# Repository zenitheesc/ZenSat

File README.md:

<h1 align="center" style="color:white; background-color:black">ZenSat</h1>
<h4 align="center">This is an Open Hardware and Software CubeSat developed by Zenith EESC-USP for the CubeDesign 2018.</h4>

<p align="center">

</p>

Aiming to participate in the first CubeDesign in 2018, Zenith designed its first nanosatellite prototype, which was named ”ZenSat”. This project was a 2U CubeSat for imaging missions in the competition. It is worth mentioning that the focus of the project was not to validate a nanosatellite for flight but to enable a first contact between the group members and the development of a nanosatellite.

<a href="https://github.com/zenitheesc/ZenSat_1.0/tree/master/ADC%20-%20Attitude%20Determination%20and%20Control"><h2> ADC - Attitude Determination and Control </h2></a>
The entire stabilization and pointing system must be done necessary to fulfill the competition missions. For this, the reading is done necessary sensors, activating a reaction wheel, which, by means of the Law of Conservation of Angular Momentum, manages to act in the attitude of the satellite.

<a href="https://github.com/zenitheesc/ZenSat_1.0/tree/master/COM%20-%20Command%20and%20Telemetry"><h2>COM - Command and Telemetry</h2></a>
It is responsible by the bidirectional telemetry in cubesat. This System has two LoRa radios, which communicate with the CTRL Subsystem

<a href="https://github.com/zenitheesc/ZenSat_1.0/tree/master/COM%20-%20Command%20and%20Telemetry"><h2>CTRL - Control</h2></a>
The Control System is the main component of the project. This system is responsible for data analysis, decision making and controlling the others systems

<a href="https://github.com/zenitheesc/ZenSat_1.0/tree/master/PS%20-%20Power%20Supply"><h2>PS - Power Supply</h2></a>
Ensures the monitoring and control of EPS panel parameters,
that is, it performs the measurement of voltage and current levels at various points on the CubeSat;
monitors the temperature of the batteries and acts to keep it always positive, in addition to
carry out communication with other subsystems.
Also it performs conversions of battery voltage levels to the levels requested within the
hardware, making the necessary distribution, as well as controlling the loading of batteries through solar panels.

<a href="https://github.com/zenitheesc/ZenSat_1.0/tree/master/STT%20-%20Structure"><h2> STT - Structure </h2></a>
Finally, we have the subsystem responsible for the physical integration of all
the subsystems described earlier. All manufacturing issues involving
the physical structure of ZenSat is the responsibility of the structures subsystem. The
determination of the materials used, the choice of manufacturing processes and display of all components, aiming at a satisfactory performance in the
vibration, are the main focuses of this subsystem

## Official Documentation

Check out the official documentation [here](https://github.com/zenitheesc/ZenSat_1.0/blob/master/ZenSat%20v.1.0.pdf).

<p align="center">

</p>
<p align = "center">
<a href="zenith.eesc@gmail.com">zenith.eesc@gmail.com</a>
</p>

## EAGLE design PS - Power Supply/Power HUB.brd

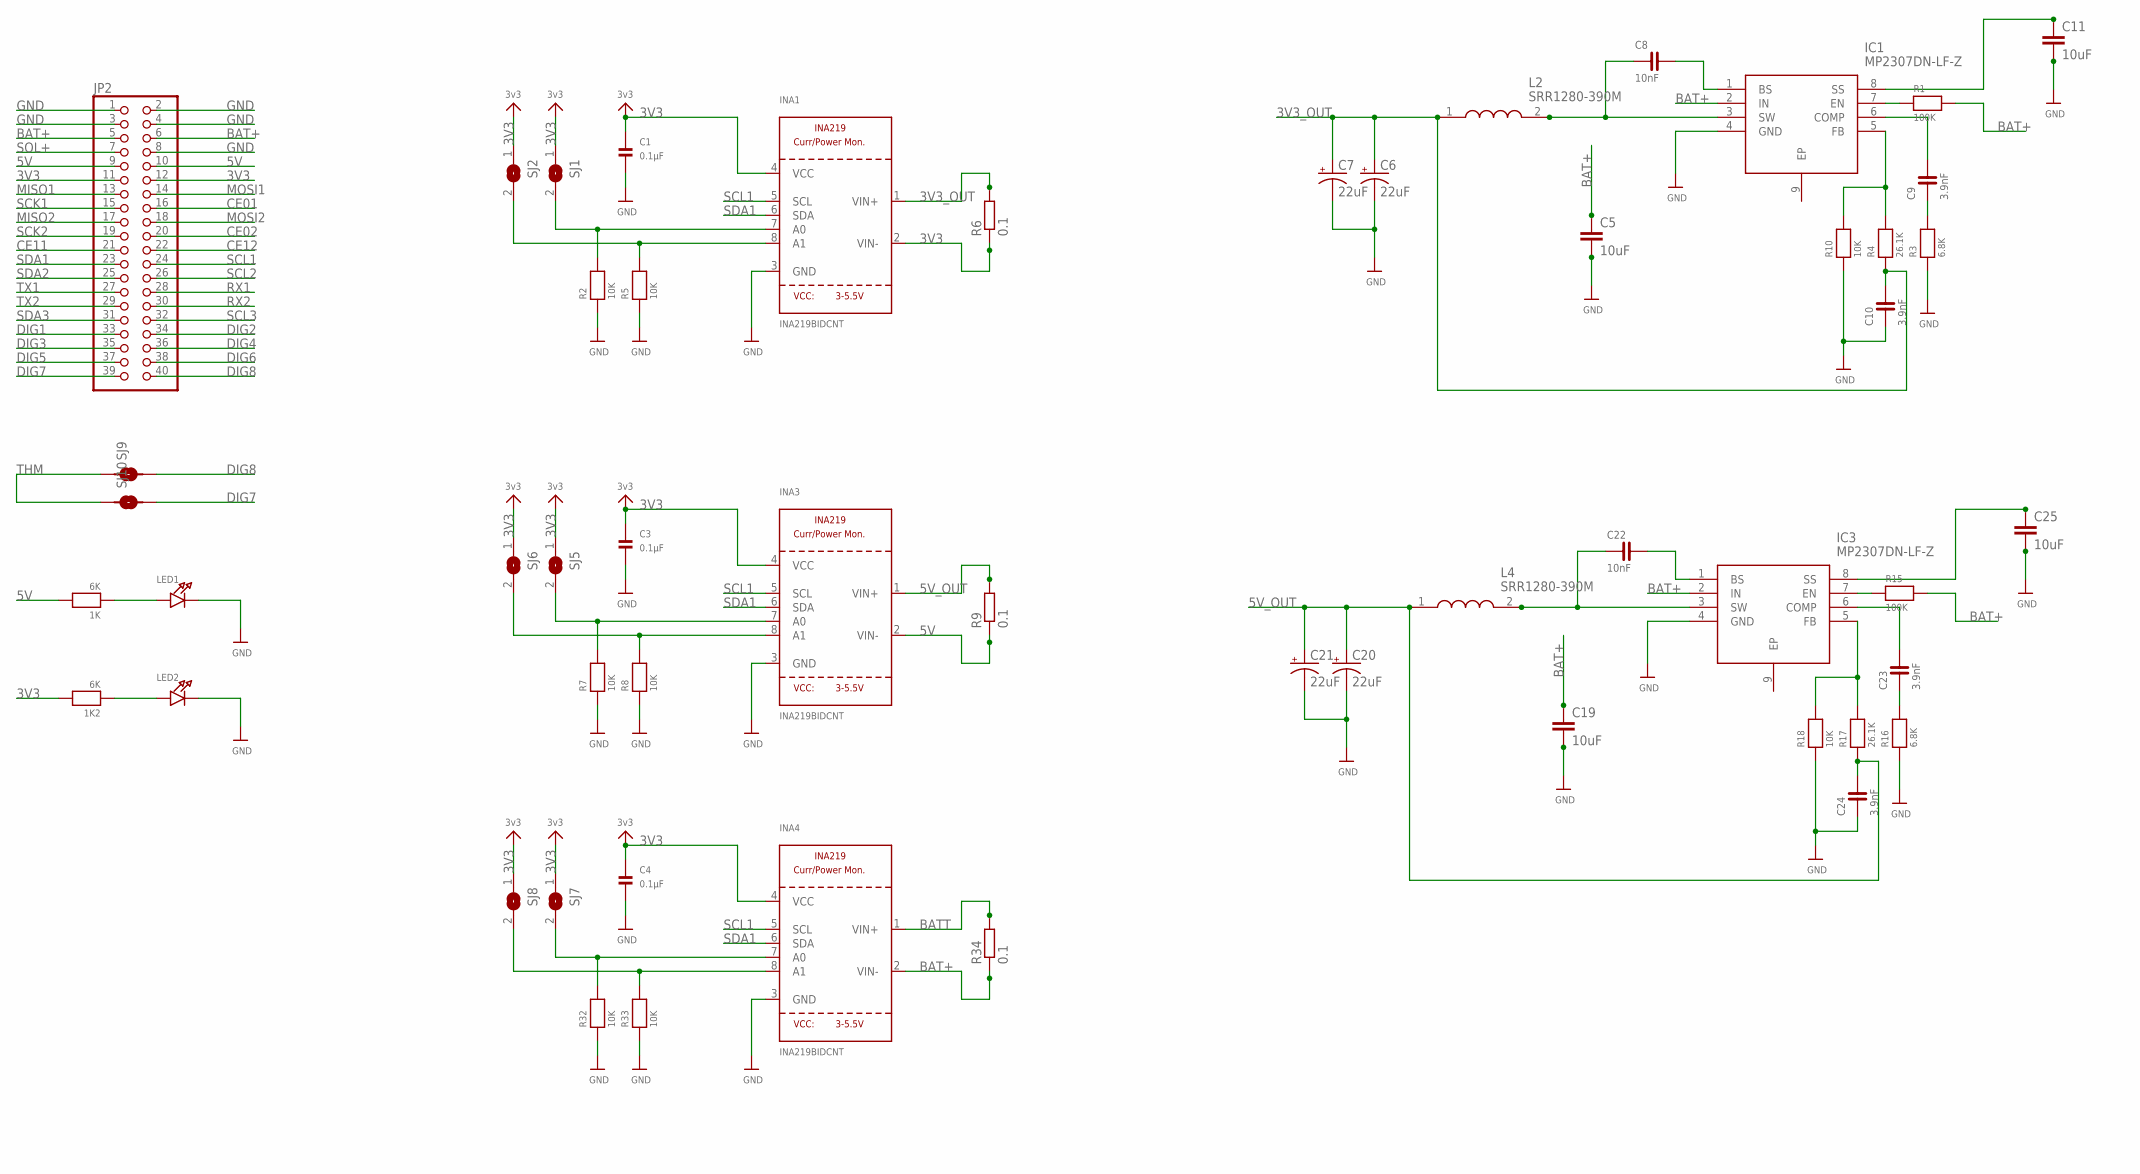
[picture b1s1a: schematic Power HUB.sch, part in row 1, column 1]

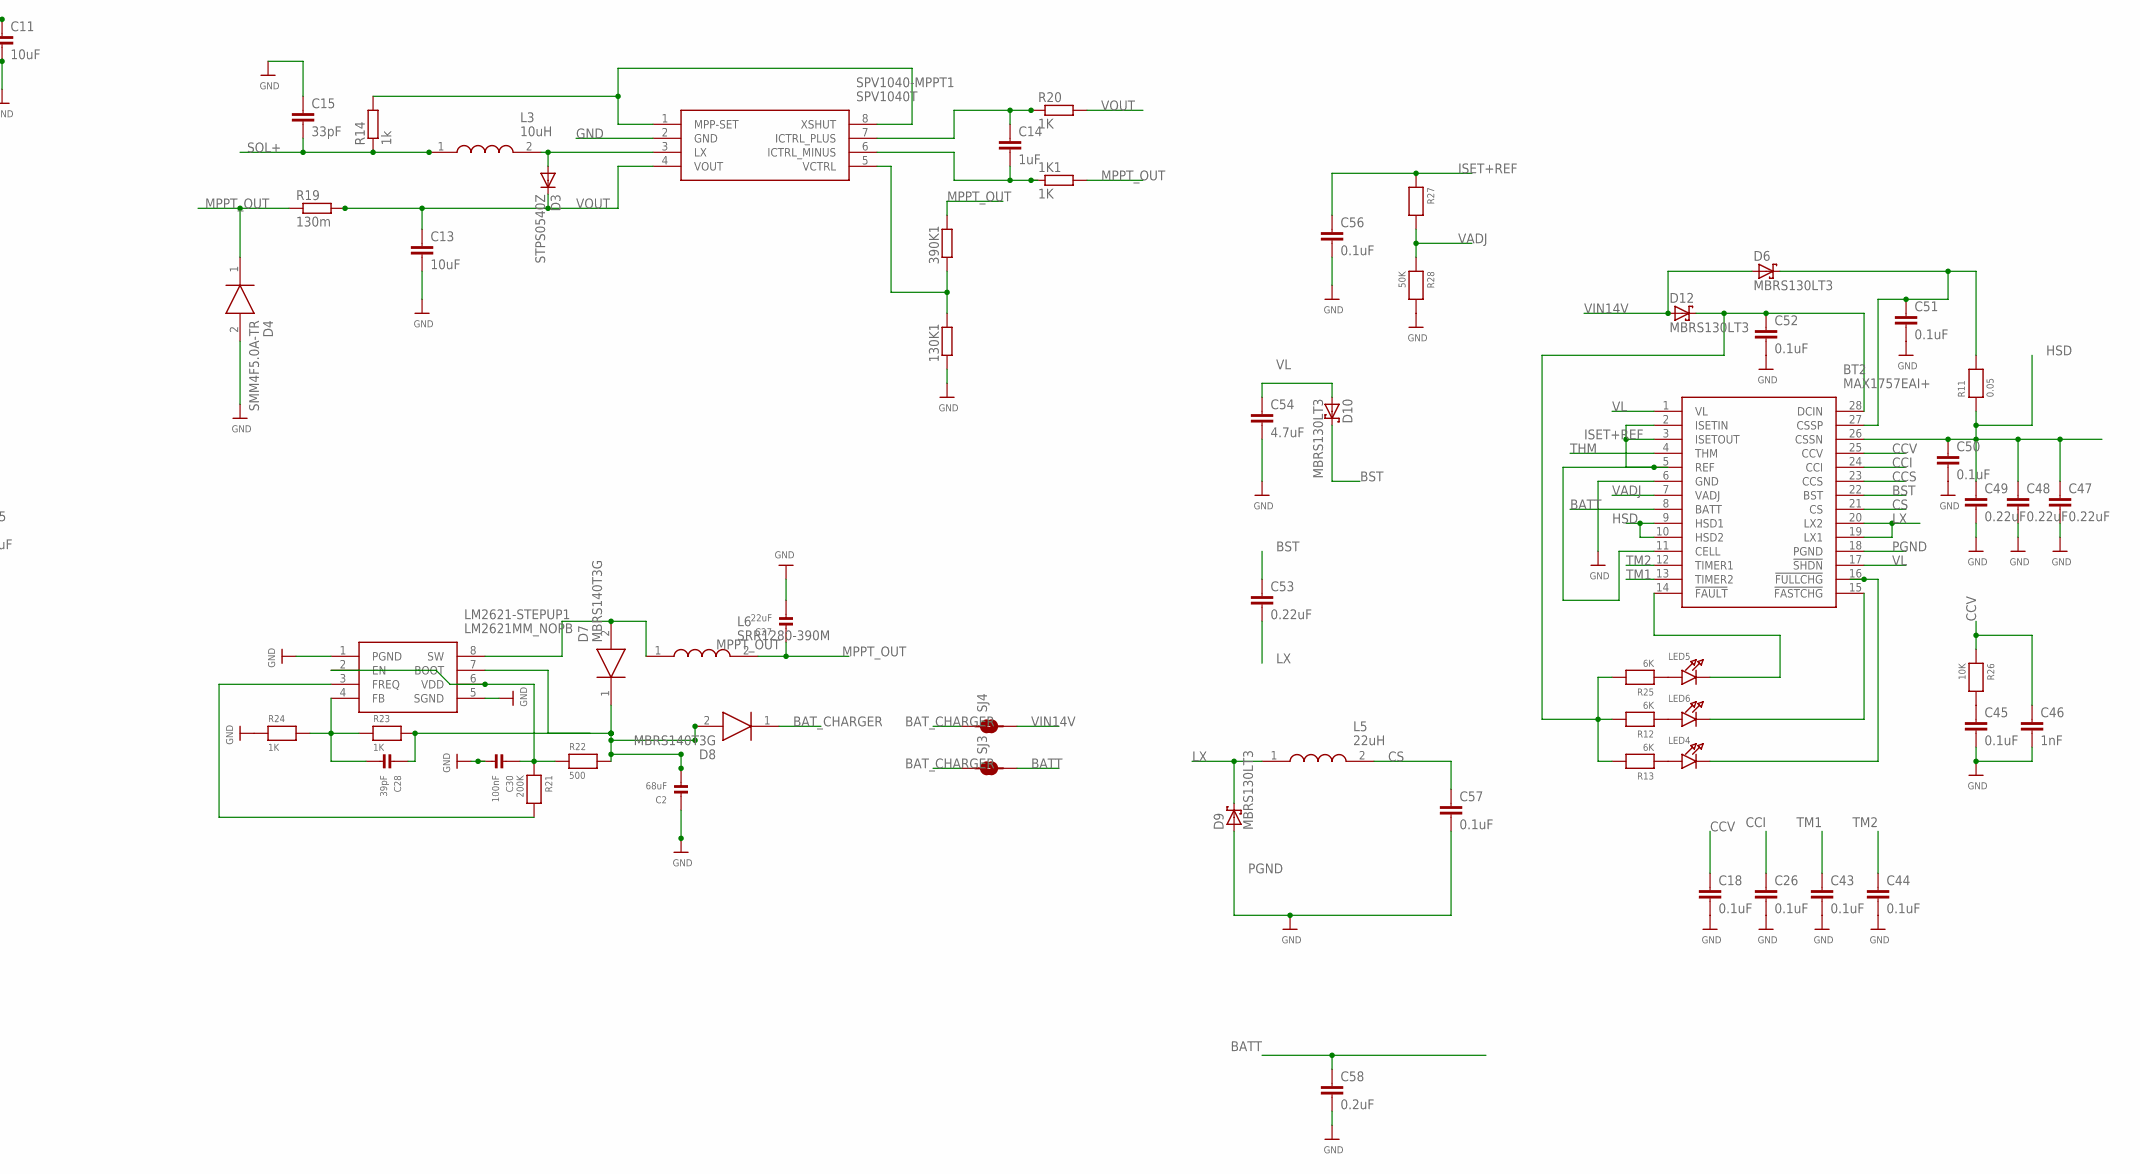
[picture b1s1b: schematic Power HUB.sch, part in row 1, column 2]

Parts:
1K, 1K2: 6K; 1206
1K1: 1K; R1206
130K1, 390K1: RR1206; R1206
BT2: MAX1757EAI+; SOP65P778X199-28N
C1, C3, C4: 0.1µF; 1206
C2: 68uF; 1206
C5, C11, C13, C19, C25: 10uF; C1206
C6, C7, C20, C21: 22uF; EIA3528
C8, C22: 10nF; 0805
C9, C10, C23, C24: 3.9nF; 0805
C14: 1uF; C1206
C15: 33pF; C1206
C18, C26, C43, C44, C45, C50, C51, C52, C56, C57: 0.1uF; C1206
C27: 22uF; 1206
C28: 39pF; 1206
C30: 100nF; 1206
C46: 1nF; C1206
C47, C48, C49, C53: 0.22uF; C1206
C54: 4.7uF; C1206
C58: 0.2uF; C1206
D3: STPS0540Z; SOD-123_MINI-SMA
D4: SMM4F5.0A-TR; STMITE
D6, D9, D10, D12: MBRS130LT3; SMB
D7, D8: MBRS140T3G; DIOM5436X247N
IC1, IC3: MP2307DN-LF-Z; SOIC127P600X170-9N
INA1, INA3, INA4: INA219BIDCNT; SOT23-8
JP2: PINHD-2X20; 2X20
L2, L4, L6: SRR1280-390M; SRR1280-220M
L3: 10uH; SRR1280-220M
L5: 22uH; INDPM4848X280N
LED1, LED2, LED4, LED5, LED6: LED1206; CHIPLED_1206
LM2621-STEPUP1: LM2621MM_NOPB; SOP65P490X110-8N
R1, R15: 100K; 1206
R2, R5, R7, R8, R10, R18, R26, R32, R33: 10K; 1206
R3, R16: 6.8K; 1206
R4, R17: 26.1K; 1206
R6, R9, R34: 0.1; R2512
R11: 0.05; 1206
R12, R13, R25: 6K; 1206
R14: 1k; R1206
R19: 130m; R1206
R20: 1K; R1206
R21: 200K; 1206
R22: 500; 1206
R23, R24: 1K; 1206
R27: RESISTOR1206; 1206
R28: 50K; 1206
SJ1, SJ2, SJ5, SJ6, SJ7, SJ8: SOLDERJUMPERREFLOW_NOPASTE; SOLDERJUMPER_REFLOW_NOPASTE
SJ3, SJ4, SJ9, SJ10: SMD-JUMPER-2
SPV1040-MPPT1: SPV1040T; SOP65P640X120-8N

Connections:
3V3: 1K2.2, C1.1, C3.1, C4.1, INA1.2 (VIN-), INA1.4 (VCC), INA3.4 (VCC), INA4.4 (VCC), JP2.11, JP2.12, R6.1, SJ1.1, SJ2.1, SJ5.1, SJ6.1, SJ7.1, SJ8.1
3V3_OUT: C6.A (+), C7.A (+), C10.2, INA1.1 (VIN+), L2.1, R4.1, R6.2
5V: 1K.2, INA3.2 (VIN-), JP2.9, JP2.10, R9.1
5V_OUT: C20.A (+), C21.A (+), C24.2, INA3.1 (VIN+), L4.1, R9.2, R17.1
BAT+: C5.1, C19.1, IC1.2 (IN), IC3.2 (IN), INA4.2 (VIN-), JP2.5, JP2.6, R1.2, R15.2, R34.1
BATT: BT2.8 (BATT), C58.1, INA4.1 (VIN+), R34.2, SJ3.2
BAT_CHARGER: D8.1 (K), SJ3.1, SJ4.1
BST: BT2.22 (BST), C53.1, D10.C
CCI: BT2.24 (CCI), C26.1
CCS: BT2.23 (CCS)
CCV: BT2.25 (CCV), C18.1, C46.1, R26.1
CE01: JP2.16
CE02: JP2.20
CE11: JP2.21
CE12: JP2.22
CS: BT2.21 (CS), C57.1, L5.2
DIG1: JP2.33
DIG2: JP2.34
DIG3: JP2.35
DIG4: JP2.36
DIG5: JP2.37
DIG6: JP2.38
DIG7: JP2.39, SJ10.2
DIG8: JP2.40, SJ9.2
GND: 130K1.1, BT2.6 (GND), C1.2, C2.1, C3.2, C4.2, C5.2, C6.C (-), C7.C (-), C10.1, C11.2, C13.2, C15.1, C19.2, C20.C (-), C21.C (-), C24.1, C25.2, C27.2, C30.2, C45.2, C46.2, C47.2, C48.2, C49.2, C54.2, C56.2, C58.2, D4.2 (A), IC1.4 (GND), IC3.4 (GND), INA1.3 (GND), INA3.3 (GND), INA4.3 (GND), JP2.1, JP2.2, JP2.3, JP2.4, JP2.8, LED1.C, LED2.C, LM2621-STEPUP1.1 (PGND), LM2621-STEPUP1.5 (SGND), R2.1, R3.1, R5.1, R7.1, R8.1, R10.1, R16.1, R18.1, R24.1, R32.1, R33.1, SPV1040-MPPT1.2 (GND)
HSD: BT2.9 (HSD1), BT2.10 (HSD2), BT2.26 (CSSN), C47.1, C48.1, C49.1, C50.1, R11.1
ISET+REF: BT2.2 (ISETIN), BT2.3 (ISETOUT), BT2.5 (REF), BT2.11 (CELL), C56.1, R27.1
LX: BT2.19 (LX1), BT2.20 (LX2), C53.2, D9.C, L5.1
MISO1: JP2.13
MISO2: JP2.17
MOSI1: JP2.14
MOSI2: JP2.18
MPPT_OUT: 1K1.2, 390K1.2, C27.1, D4.1 (K), L6.2, R19.1
unnamed: INA1.8 (A1), R5.2, SJ2.2
unnamed: INA1.7 (A0), R2.2, SJ1.2
unnamed: C8.2, IC1.1 (BS)
unnamed: C11.1, IC1.8 (SS)
unnamed: INA3.8 (A1), R8.2, SJ6.2
unnamed: INA3.7 (A0), R7.2, SJ5.2
unnamed: C8.1, IC1.3 (SW), L2.2
unnamed: IC1.7 (EN), R1.1
unnamed: C9.2, IC1.6 (COMP)
unnamed: C9.1, R3.2
unnamed: IC1.5 (FB), R4.2, R10.2
unnamed: 1K2.1, LED2.A
unnamed: 1K.1, LED1.A
unnamed: BT2.28 (DCIN), C52.1, D12.C, R12.2, R13.2, R25.2
unnamed: BT2.14 (!FAULT), LED5.C
unnamed: D3.A, L3.2, SPV1040-MPPT1.3 (LX)
unnamed: R14.2, SPV1040-MPPT1.1 (MPP-SET), SPV1040-MPPT1.8 (XSHUT)
unnamed: C22.2, IC3.1 (BS)
unnamed: C25.1, IC3.8 (SS)
unnamed: C22.1, IC3.3 (SW), L4.2
unnamed: IC3.7 (EN), R15.1
unnamed: C23.2, IC3.6 (COMP)
unnamed: C23.1, R16.2
unnamed: IC3.5 (FB), R17.2, R18.2
unnamed: C14.1, R20.1, SPV1040-MPPT1.7 (ICTRL_PLUS)
unnamed: 1K1.1, C14.2, SPV1040-MPPT1.6 (ICTRL_MINUS)
unnamed: 130K1.2, 390K1.1, SPV1040-MPPT1.5 (VCTRL)
unnamed: BT2.15 (!FASTCHG), LED6.C
unnamed: BT2.16 (!FULLCHG), LED4.C
unnamed: INA4.8 (A1), R33.2, SJ8.2
unnamed: C2.2, D7.1 (K), D8.2 (A), LM2621-STEPUP1.7 (BOOT), R22.2
unnamed: C30.1, LM2621-STEPUP1.2 (EN), LM2621-STEPUP1.6 (VDD), R21.1, R22.1
unnamed: LM2621-STEPUP1.3 (FREQ), R21.2
unnamed: C28.2, LM2621-STEPUP1.4 (FB), R23.1, R24.2
unnamed: C28.1, R23.2
unnamed: D7.2 (A), L6.1, LM2621-STEPUP1.8 (SW)
unnamed: INA4.7 (A0), R32.2, SJ7.2
unnamed: BT2.27 (CSSP), C51.1, D6.C, R11.2
PGND: BT2.18 (PGND), C57.2, D9.A
RX1: JP2.28
RX2: JP2.30
SCK1: JP2.15
SCK2: JP2.19
SCL1: INA1.5 (SCL), INA3.5 (SCL), INA4.5 (SCL), JP2.24
SCL2: JP2.26
SCL3: JP2.32
SDA1: INA1.6 (SDA), INA3.6 (SDA), INA4.6 (SDA), JP2.23
SDA2: JP2.25
SDA3: JP2.31
SOL+: C15.2, JP2.7, L3.1, R14.1
THM: BT2.4 (THM), SJ9.1, SJ10.1
TM1: BT2.13 (TIMER2), C43.1
TM2: BT2.12 (TIMER1), C44.1
TX1: JP2.27
TX2: JP2.29
VADJ: BT2.7 (VADJ), R27.2, R28.1
VIN14V: D6.A, D12.A, SJ4.2
VL: BT2.1 (VL), BT2.17 (!SHDN), C54.1, D10.A
VOUT: C13.1, D3.C, R19.2, R20.2, SPV1040-MPPT1.4 (VOUT)

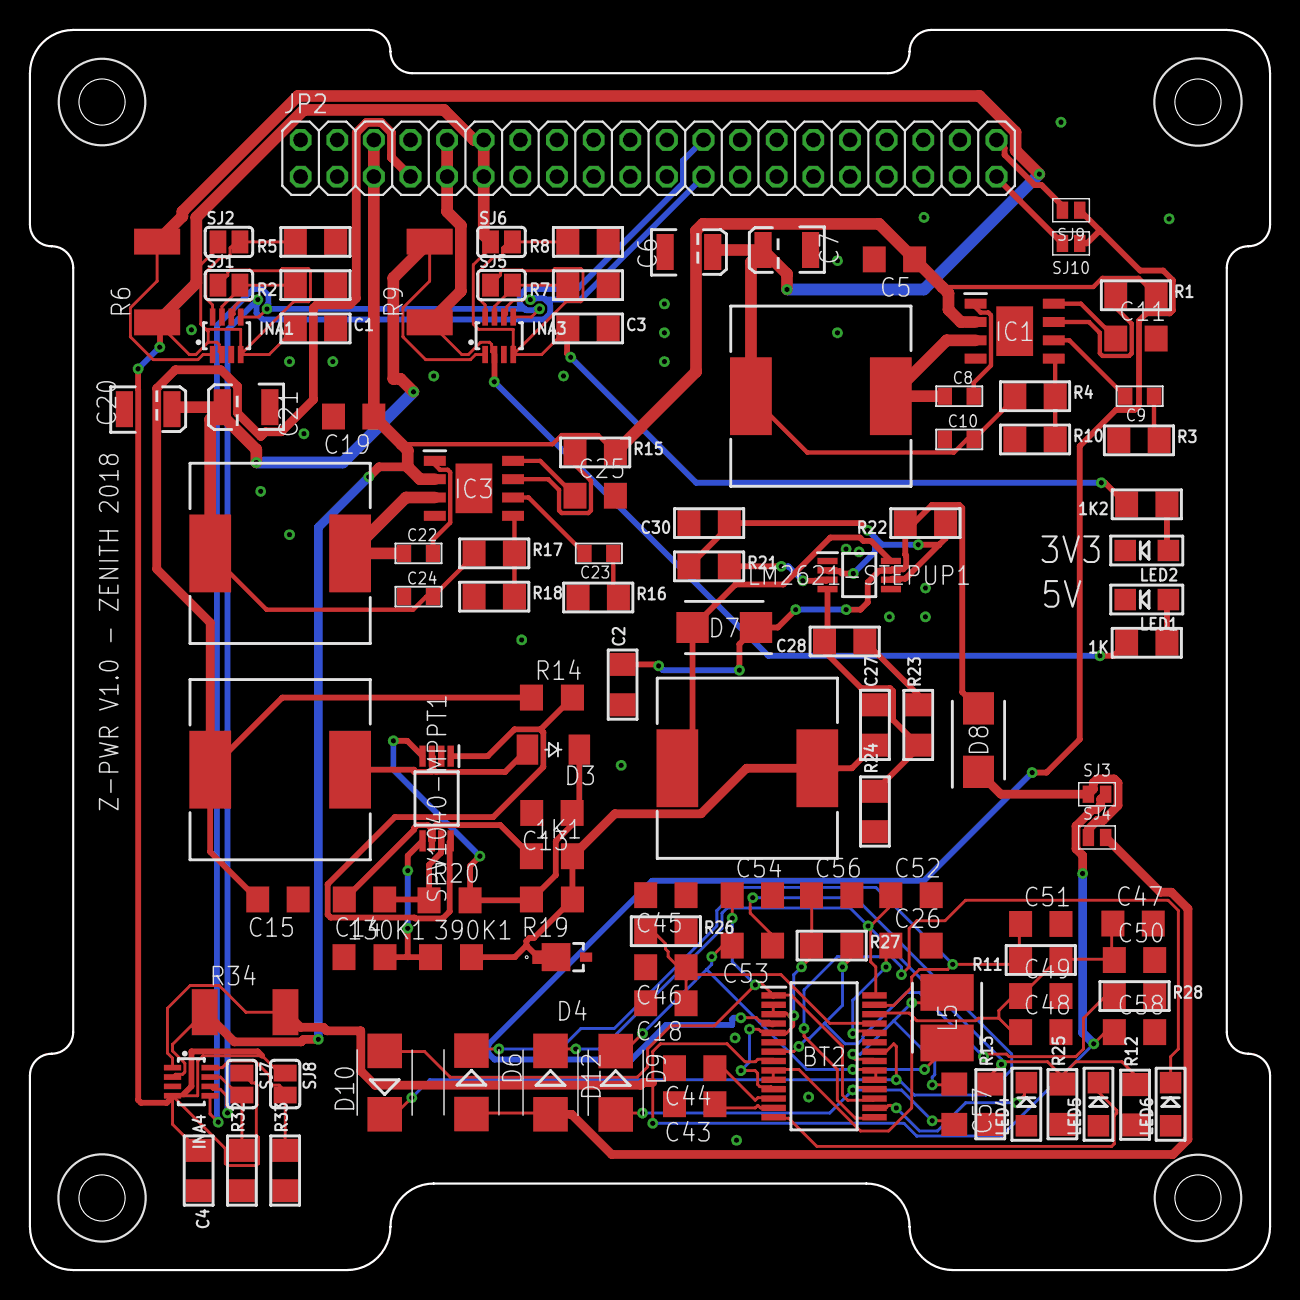
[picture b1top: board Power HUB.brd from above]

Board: 2 copper layers, 86.0 x 86.0 mm, 114 parts (0 on the bottom side), 67 nets.

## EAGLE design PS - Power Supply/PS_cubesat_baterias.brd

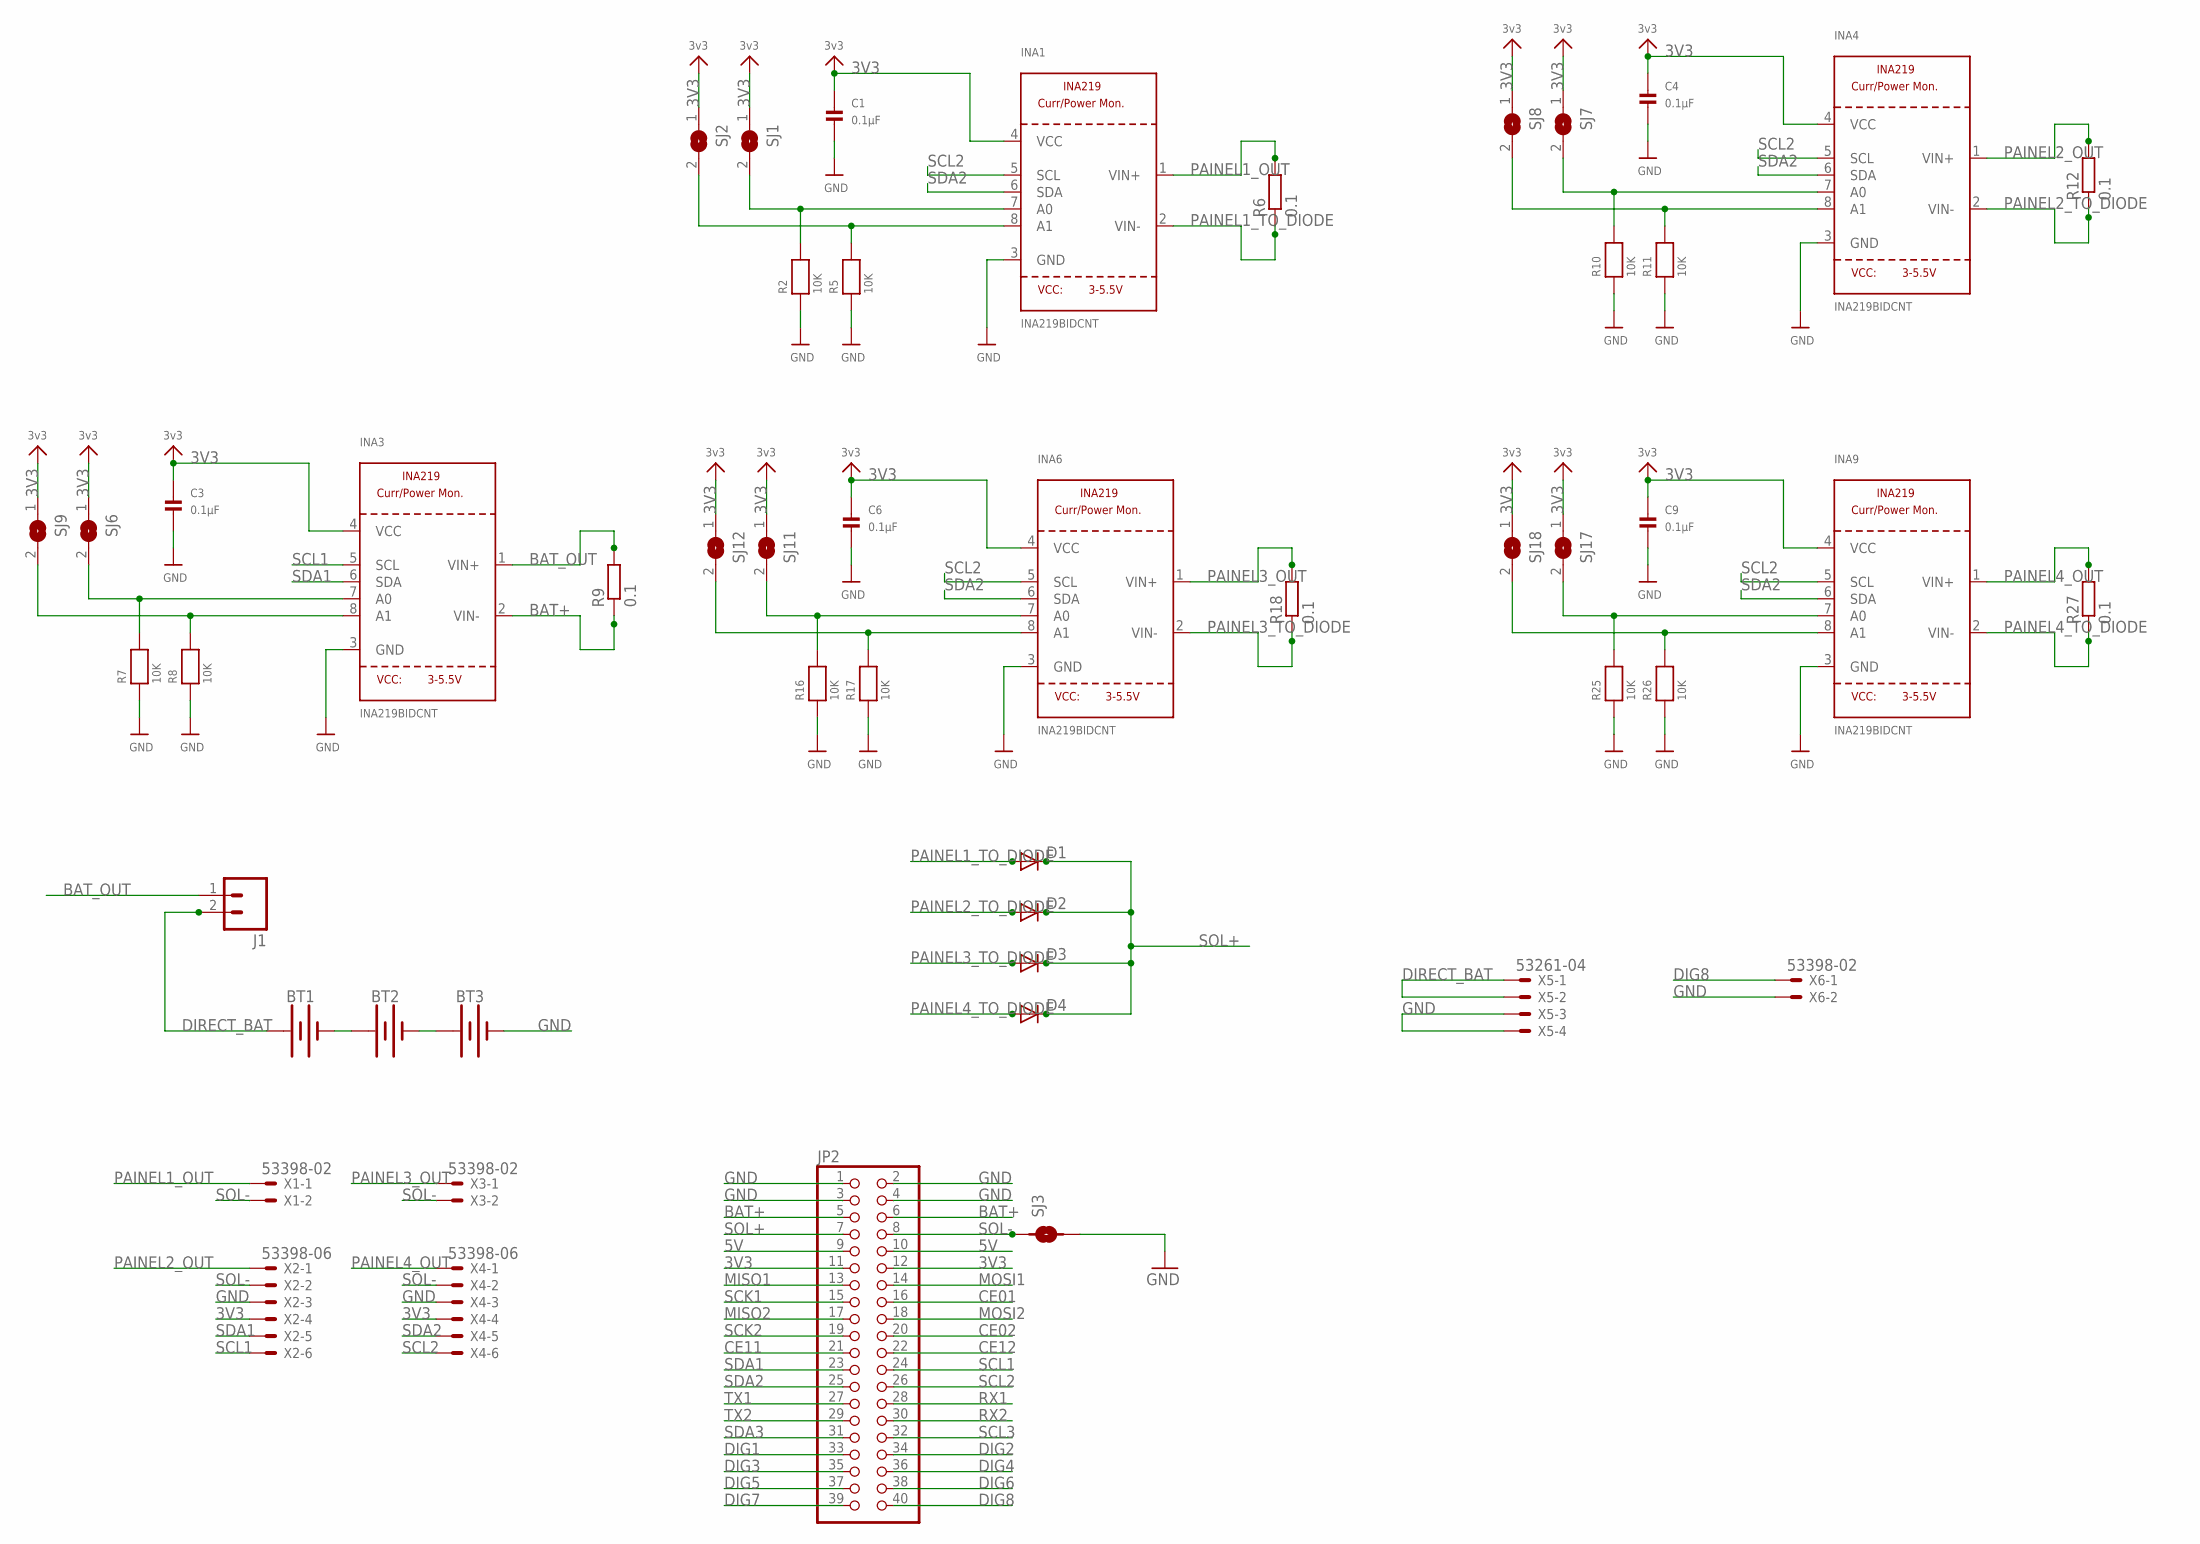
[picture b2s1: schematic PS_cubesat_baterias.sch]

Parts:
BT1, BT2, BT3: BATTERY-18650; BATTERY_18650-HOLDER
C1, C3, C4, C6, C9: 0.1µF; 1206
D1, D2, D3, D4: DIODE-DO-214AC; DO-214AC
INA1, INA3, INA4, INA6, INA9: INA219BIDCNT; SOT23-8
J1: M02JST-PTH-VERT; JST-2-PTH-VERT
JP2: PINHD-2X20; 2X20
R2, R5, R7, R8, R10, R11, R16, R17, R25, R26: 10K; 1206
R6, R9, R12, R18, R27: 0.1; R2512
SJ1, SJ2, SJ6, SJ7, SJ8, SJ9, SJ11, SJ12, SJ17, SJ18: SOLDERJUMPERREFLOW_NOPASTE; SOLDERJUMPER_REFLOW_NOPASTE
SJ3: SMD-JUMPER-2
X1, X3, X6: 53398-02
X2, X4: 53398-06
X5: 53261-04

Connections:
3V3: C1.1, C3.1, C4.1, C6.1, C9.1, INA1.4 (VCC), INA3.4 (VCC), INA4.4 (VCC), INA6.4 (VCC), INA9.4 (VCC), JP2.11, JP2.12, SJ1.1, SJ2.1, SJ6.1, SJ7.1, SJ8.1, SJ9.1, SJ11.1, SJ12.1, SJ17.1, SJ18.1, X2.4, X4.4
5V: JP2.9, JP2.10
BAT+: INA3.2 (VIN-), JP2.5, JP2.6, R9.1
BAT_OUT: INA3.1 (VIN+), J1.1, R9.2
CE01: JP2.16
CE02: JP2.20
CE11: JP2.21
CE12: JP2.22
DIG1: JP2.33
DIG2: JP2.34
DIG3: JP2.35
DIG4: JP2.36
DIG5: JP2.37
DIG6: JP2.38
DIG7: JP2.39
DIG8: JP2.40, X6.1
DIRECT_BAT: BT1.PWR@1 (+), J1.2, X5.1, X5.2
GND: BT3.GND@1 (-), C1.2, C3.2, C4.2, C6.2, C9.2, INA1.3 (GND), INA3.3 (GND), INA4.3 (GND), INA6.3 (GND), INA9.3 (GND), JP2.1, JP2.2, JP2.3, JP2.4, R2.1, R5.1, R7.1, R8.1, R10.1, R11.1, R16.1, R17.1, R25.1, R26.1, SJ3.2, X2.3, X4.3, X5.3, X5.4, X6.2
MISO1: JP2.13
MISO2: JP2.17
MOSI1: JP2.14
MOSI2: JP2.18
unnamed: BT1.GND@1 (-), BT2.PWR@1 (+)
unnamed: BT2.GND@1 (-), BT3.PWR@1 (+)
unnamed: INA1.8 (A1), R5.2, SJ2.2
unnamed: INA1.7 (A0), R2.2, SJ1.2
unnamed: INA3.8 (A1), R8.2, SJ9.2
unnamed: INA3.7 (A0), R7.2, SJ6.2
unnamed: INA4.8 (A1), R11.2, SJ8.2
unnamed: INA4.7 (A0), R10.2, SJ7.2
unnamed: INA6.8 (A1), R17.2, SJ12.2
unnamed: INA6.7 (A0), R16.2, SJ11.2
unnamed: INA9.8 (A1), R26.2, SJ18.2
unnamed: INA9.7 (A0), R25.2, SJ17.2
PAINEL1_OUT: INA1.1 (VIN+), R6.2, X1.1
PAINEL1_TO_DIODE: D1.A, INA1.2 (VIN-), R6.1
PAINEL2_OUT: INA4.1 (VIN+), R12.2, X2.1
PAINEL2_TO_DIODE: D2.A, INA4.2 (VIN-), R12.1
PAINEL3_OUT: INA6.1 (VIN+), R18.2, X3.1
PAINEL3_TO_DIODE: D3.A, INA6.2 (VIN-), R18.1
PAINEL4_OUT: INA9.1 (VIN+), R27.2, X4.1
PAINEL4_TO_DIODE: D4.A, INA9.2 (VIN-), R27.1
RX1: JP2.28
RX2: JP2.30
SCK1: JP2.15
SCK2: JP2.19
SCL1: INA3.5 (SCL), JP2.24, X2.6
SCL2: INA1.5 (SCL), INA4.5 (SCL), INA6.5 (SCL), INA9.5 (SCL), JP2.26, X4.6
SCL3: JP2.32
SDA1: INA3.6 (SDA), JP2.23, X2.5
SDA2: INA1.6 (SDA), INA4.6 (SDA), INA6.6 (SDA), INA9.6 (SDA), JP2.25, X4.5
SDA3: JP2.31
SOL+: D1.C, D2.C, D3.C, D4.C, JP2.7
SOL-: JP2.8, SJ3.1, X1.2, X2.2, X3.2, X4.2
TX1: JP2.27
TX2: JP2.29

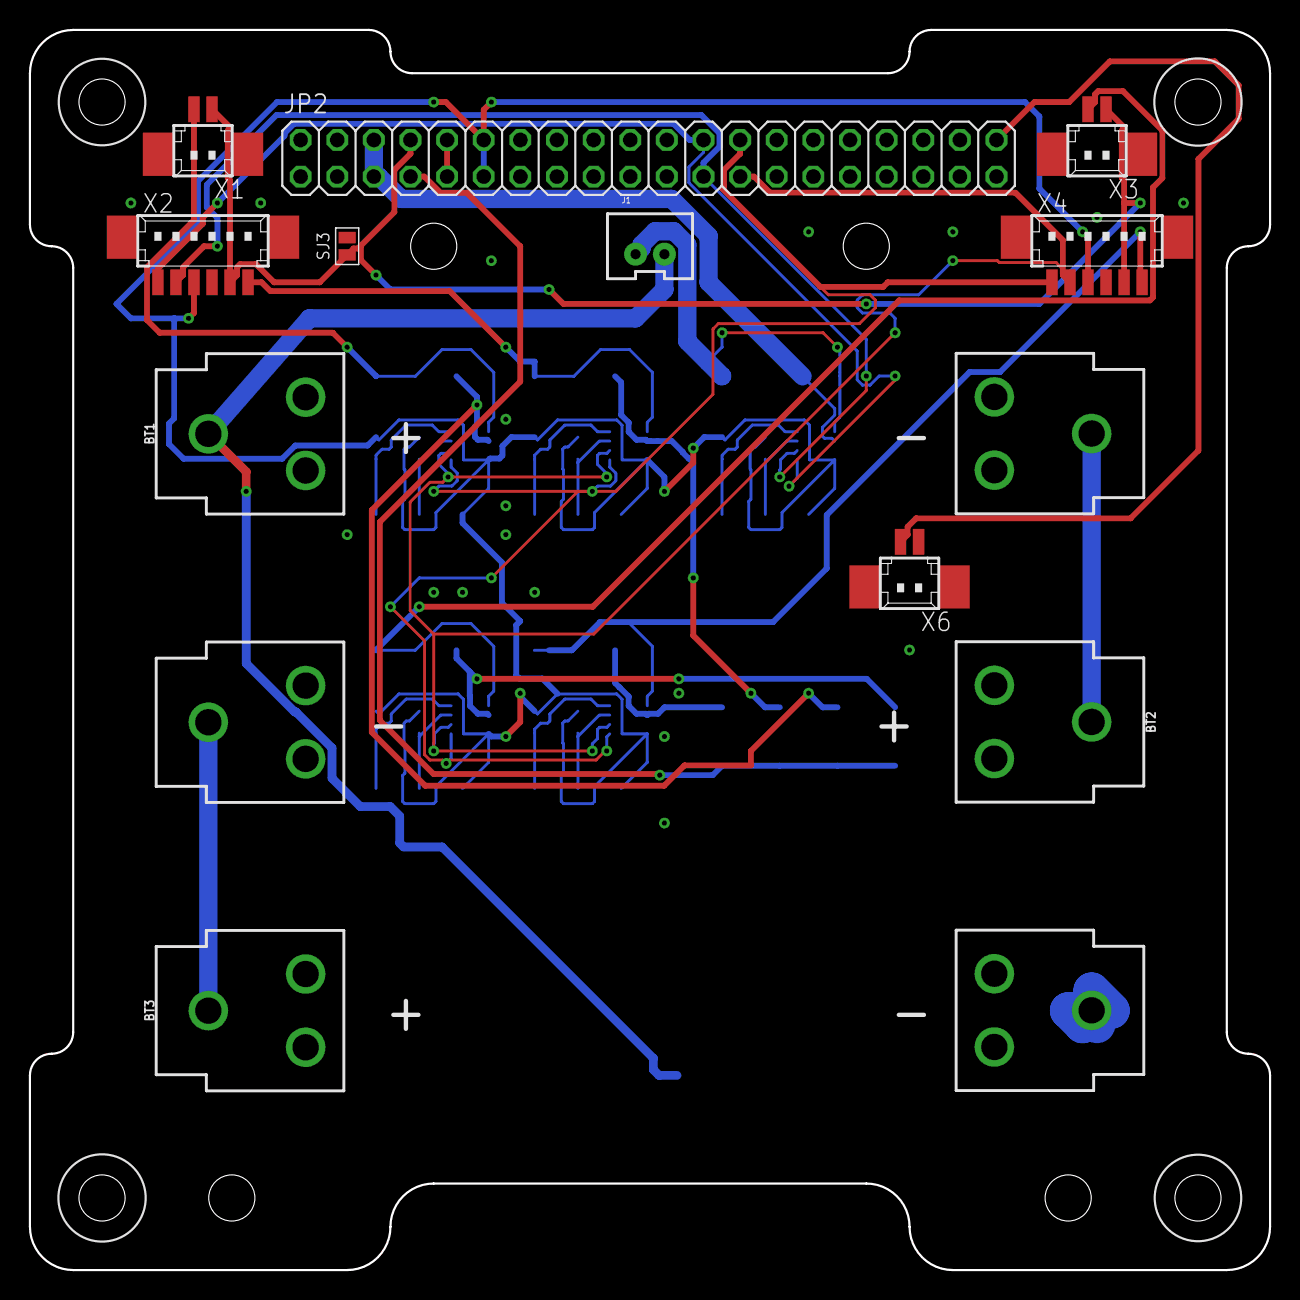
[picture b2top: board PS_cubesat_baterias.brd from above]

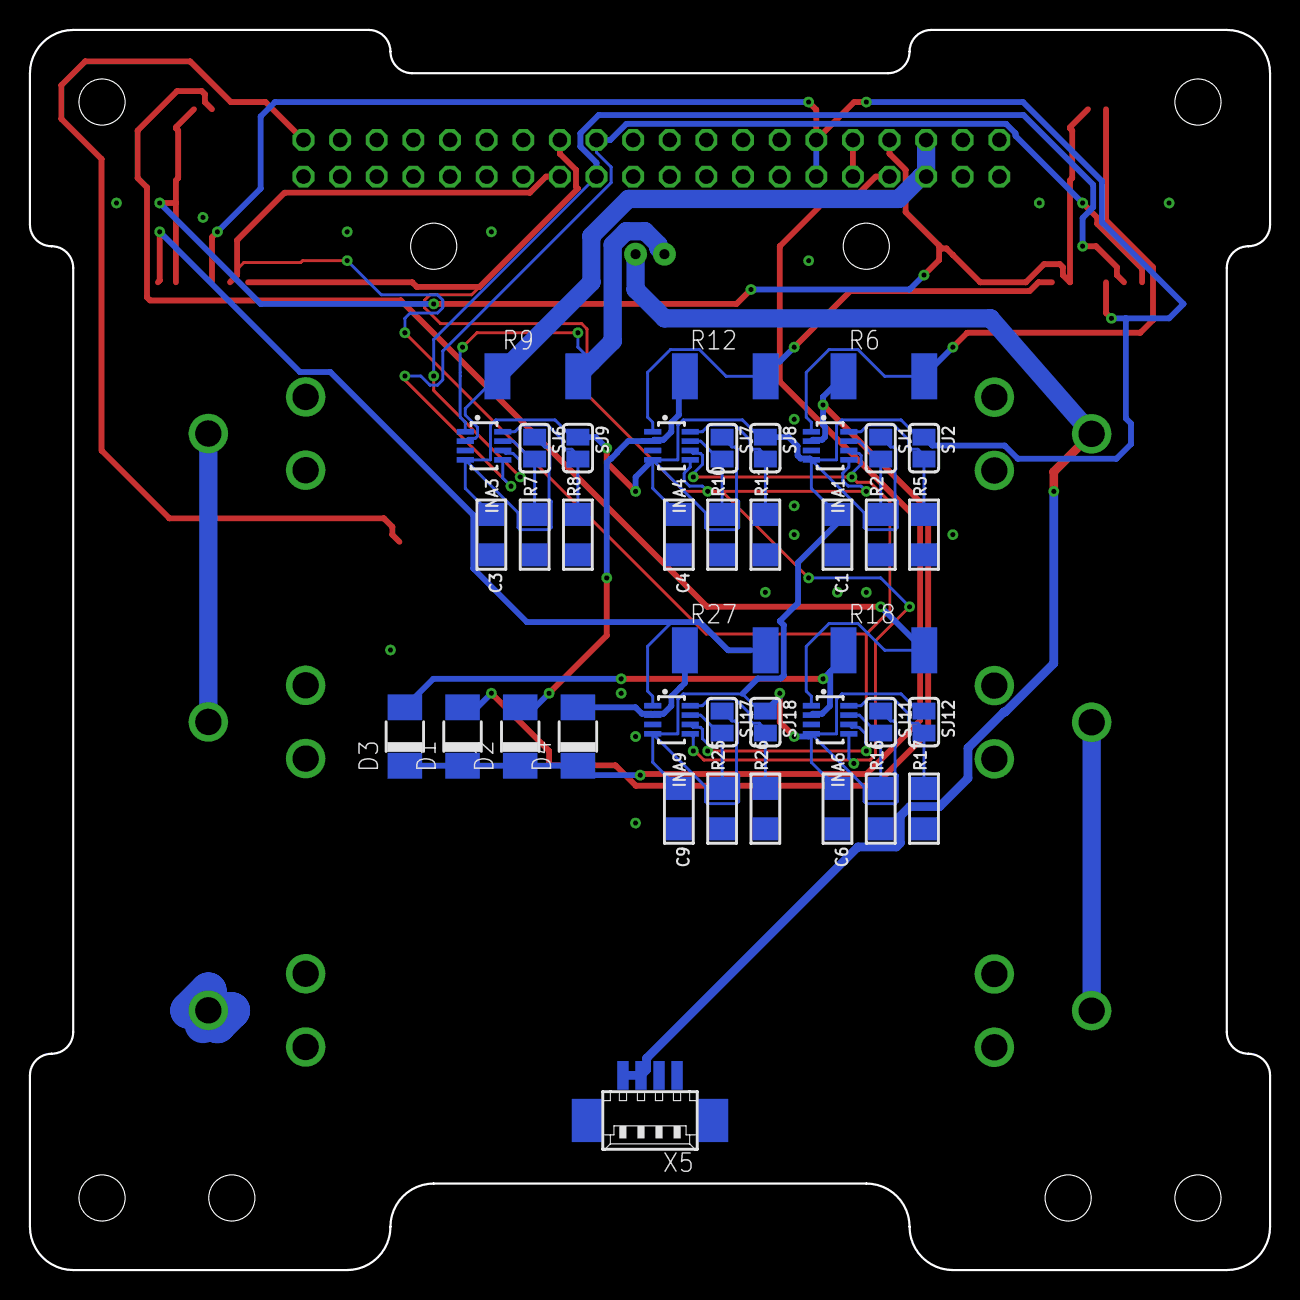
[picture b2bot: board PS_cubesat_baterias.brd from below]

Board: 2 copper layers, 86.0 x 86.0 mm, 51 parts (40 on the bottom side), 33 nets.

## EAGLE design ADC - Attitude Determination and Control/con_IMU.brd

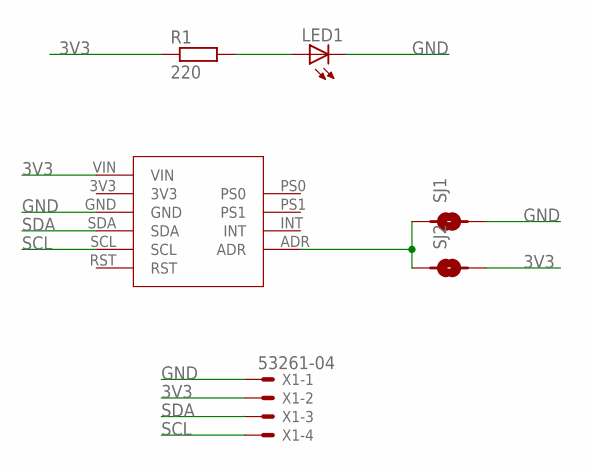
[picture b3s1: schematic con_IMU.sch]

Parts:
LED1: LEDCHIPLED_1206; CHIPLED_1206
R1: 220; R1206
SJ1, SJ2: SMD-JUMPER-2
U$1: BNO055; BNO055_MOD
X1: 53261-04

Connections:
3V3: R1.1, SJ2.2, U$1.VIN, X1.2
GND: LED1.C, SJ1.2, U$1.GND, X1.1
unnamed: LED1.A, R1.2
unnamed: SJ1.1, SJ2.1, U$1.ADR
SCL: U$1.SCL, X1.4
SDA: U$1.SDA, X1.3

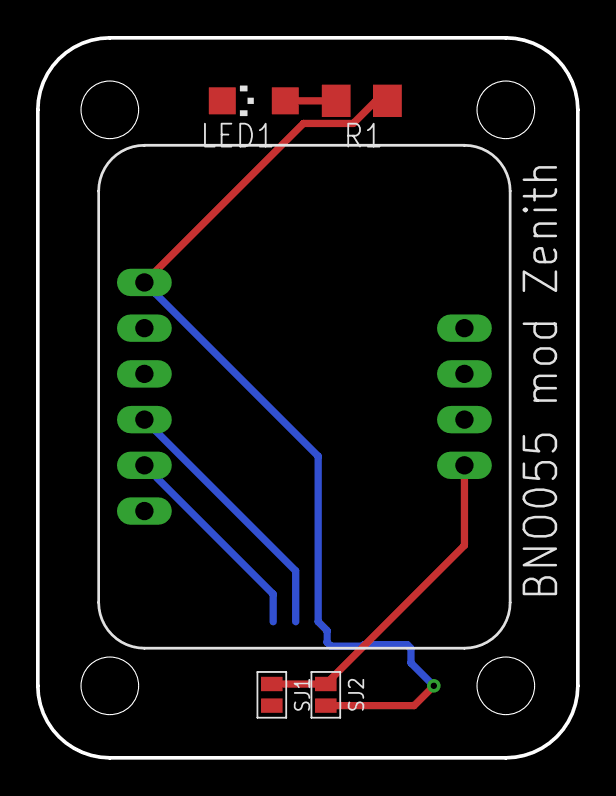
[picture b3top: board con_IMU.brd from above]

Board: 2 copper layers, 30.0 x 40.0 mm, 6 parts (1 on the bottom side), 6 nets.

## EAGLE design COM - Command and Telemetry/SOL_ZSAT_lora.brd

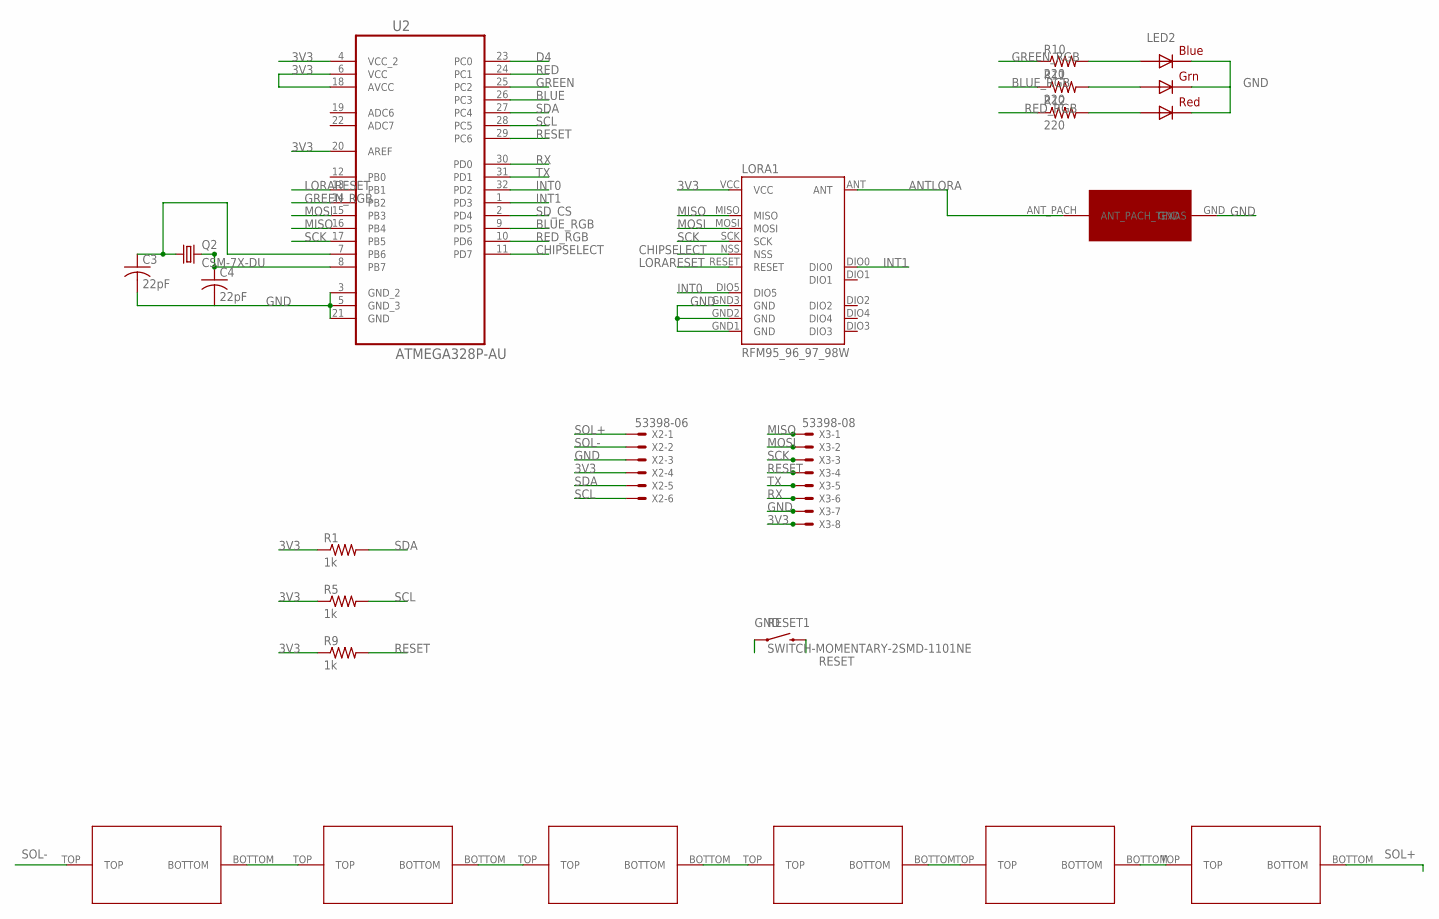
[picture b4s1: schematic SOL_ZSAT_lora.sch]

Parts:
C3, C4: 22pF; C0603
LED2: RGBLED5050
LORA1: RFM95_96_97_98W
Q2: CSM-7X-DU
R1, R5, R9: 1k; M1206
R10, R11, R12: 220; R0603
RESET1: SWITCH-MOMENTARY-2SMD-1101NE; TACTILE-SWITCH-1101NE
U2: ATMEGA328P-AU; QFP80P900X900X120-32N
U$1, U$2, U$3, U$4, U$5, U$6: SOL_26X52; SOLAR_52X26
U$7: 915MHZ_PACH_TEXAS
X2: 53398-06
X3: 53398-08

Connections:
3V3: LORA1.VCC, R1.1, R5.1, R9.1, U2.4 (VCC_2), U2.6 (VCC), U2.18 (AVCC), U2.20 (AREF), X2.4, X3.8
ANTLORA: LORA1.ANT, U$7.ANT_PACH (ANT_PACH_TEXAS)
BLUE: U2.26 (PC3)
BLUE_RGB: R11.1, U2.9 (PD5)
CHIPSELECT: LORA1.NSS, U2.11 (PD7)
D4: U2.23 (PC0)
GND: C3.2, C4.2, LED2.4 (BLUE_C), LED2.5 (RED_C), LED2.6 (GREEN_C), LORA1.GND1 (GND), LORA1.GND2 (GND), LORA1.GND3 (GND), RESET1.1, U2.3 (GND_2), U2.5 (GND_3), U2.21 (GND), U$7.GND, X2.3, X3.7
GREEN: U2.25 (PC2)
GREEN_RGB: R10.1, U2.14 (PB2)
INT0: LORA1.DIO5, U2.32 (PD2)
INT1: LORA1.DIO0, U2.1 (PD3)
LORARESET: LORA1.RESET, U2.13 (PB1)
MISO: LORA1.MISO, U2.16 (PB4), X3.1
MOSI: LORA1.MOSI, U2.15 (PB3), X3.2
unnamed: U$1.BOTTOM, U$2.TOP
unnamed: U$2.BOTTOM, U$3.TOP
unnamed: U$3.BOTTOM, U$4.TOP
unnamed: U$4.BOTTOM, U$5.TOP
unnamed: U$5.BOTTOM, U$6.TOP
unnamed: C4.1, Q2.2, U2.8 (PB7)
unnamed: C3.1, Q2.1, U2.7 (PB6)
unnamed: LED2.3 (BLUE_A), R10.2
unnamed: LED2.1 (GREEN_A), R11.2
unnamed: LED2.2 (RED_A), R12.2
RED: U2.24 (PC1)
RED_RGB: R12.1, U2.10 (PD6)
RESET: R9.2, RESET1.2, U2.29 (PC6), X3.4
RX: U2.30 (PD0), X3.6
SCK: LORA1.SCK, U2.17 (PB5), X3.3
SCL: R5.2, U2.28 (PC5), X2.6
SDA: R1.2, U2.27 (PC4), X2.5
SD_CS: U2.2 (PD4)
SOL+: U$6.BOTTOM, X2.1
SOL-: U$1.TOP, X2.2
TX: U2.31 (PD1), X3.5

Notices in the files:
parts and their libraries:
SparkFun-Electromechanical: Licensing: Creative Commons ShareAlike 4.0 International - https://creativecommons.org/licenses/by-sa/4.0
microbuilder: This work is placed in the public domain, and may be freely used for commercial and non-commercial work with the following conditions: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
